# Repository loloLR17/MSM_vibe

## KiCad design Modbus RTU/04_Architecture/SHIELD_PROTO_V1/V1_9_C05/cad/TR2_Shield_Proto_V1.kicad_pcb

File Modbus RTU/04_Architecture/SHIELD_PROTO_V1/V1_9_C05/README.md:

# TR2 shield V1.9 — candidat corrigé sur CAO officielle C05

**NON LIBÉRÉ POUR FABRICATION.** Lire [la décision et les contrôles](DECISION_V19.md), [la provenance ST](PROVENANCE.md) et [le gabarit corrigé100%](exports/GABARITS_C05_V19_100POURCENT.pdf).

Ce dossier est le nouveau candidat éditable autonome. Les fichiers du dossierparent V1.4 et ses exports V1.8 sont historiques et préservés ; ne pas les prendre pour la correctionV1.9. Schéma/projet copiés sans changement électrique, PCB et routes localement corrigés. Le cartouche du schéma demeureV1.4 car le schéma est inchangé ; le PCB porteV1.9DRAFT.

Pour reproduire dans une copie isolée de ce dossier, **conserver le `design.json` V1.9 fourni**. Retirer le cuivre du **PCB candidat uniquement** avec `tools/strip_candidate_copper.py <candidatePCB>`, puis appliquer les positions absolues et trous avec `tools/patch_native.py <dossierV19>` (PythonKiCad10). Exécuter `tools/route_local.py` (Python+numpy+shapely ; lit les routes historiques du dossierparent), puis `tools/apply_routes.py <dossierV19>` avecPythonKiCad. Exécuter `tools/export_design.py`, `tools/read_board.py <dossierV19>` avecPythonKiCad, puis `tools/verify_exports.py`, `tools/verify_v19.py` et `tools/generate_templates.py` avecPyMuPDF. `patch_native` écrit `docs/pcb_geometry.json`, base de l’adaptation locale. L’application des routes suppose un candidat sans anciencuivre pour éviter un double routage. Le schéma et le projet fournis sont inchangés ; ne pas remplacer le designV1.9 par celuiV1.4. Ne jamais lancer ces scripts sur les originaux historiques.

Les originauxST restent en dehorsGit, sous `/home/lolo/dev/msm/reports/TR2-shield-v19-20261105`. Pour reproduire l’extraction CFB/ODB : `PYTHONPATH=/home/lolo/dev/msm/cache/shield-pylibs python3 tools/extract_st.py <ce-repertoire>` après avoir vérifié les deux SHA256 et extrait les archives conformément àPROVENANCE. Les preuves d’échecs et corrections de l’outillage sont conservées ; aucun test ou règle historique affaibli.

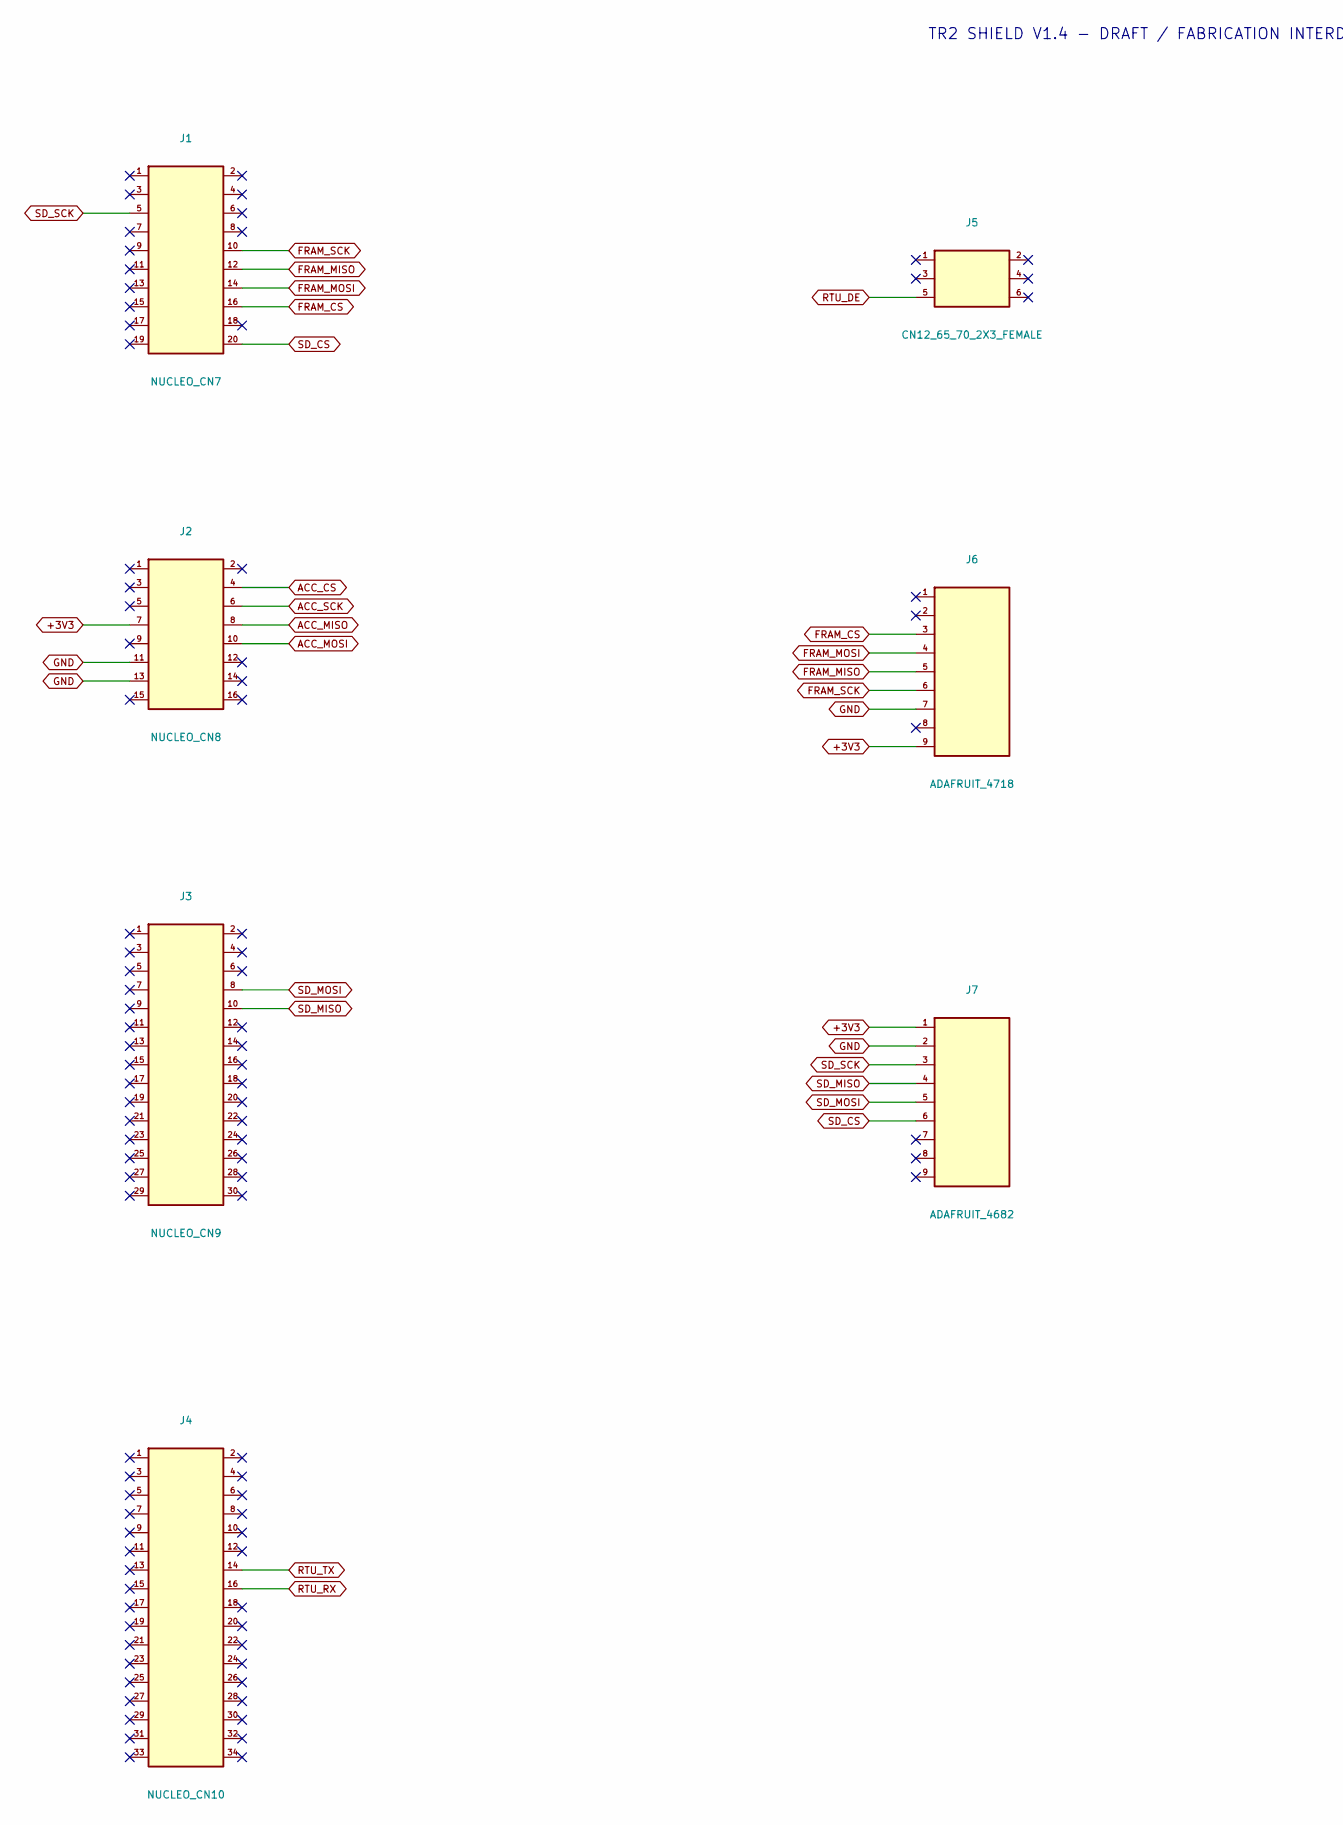
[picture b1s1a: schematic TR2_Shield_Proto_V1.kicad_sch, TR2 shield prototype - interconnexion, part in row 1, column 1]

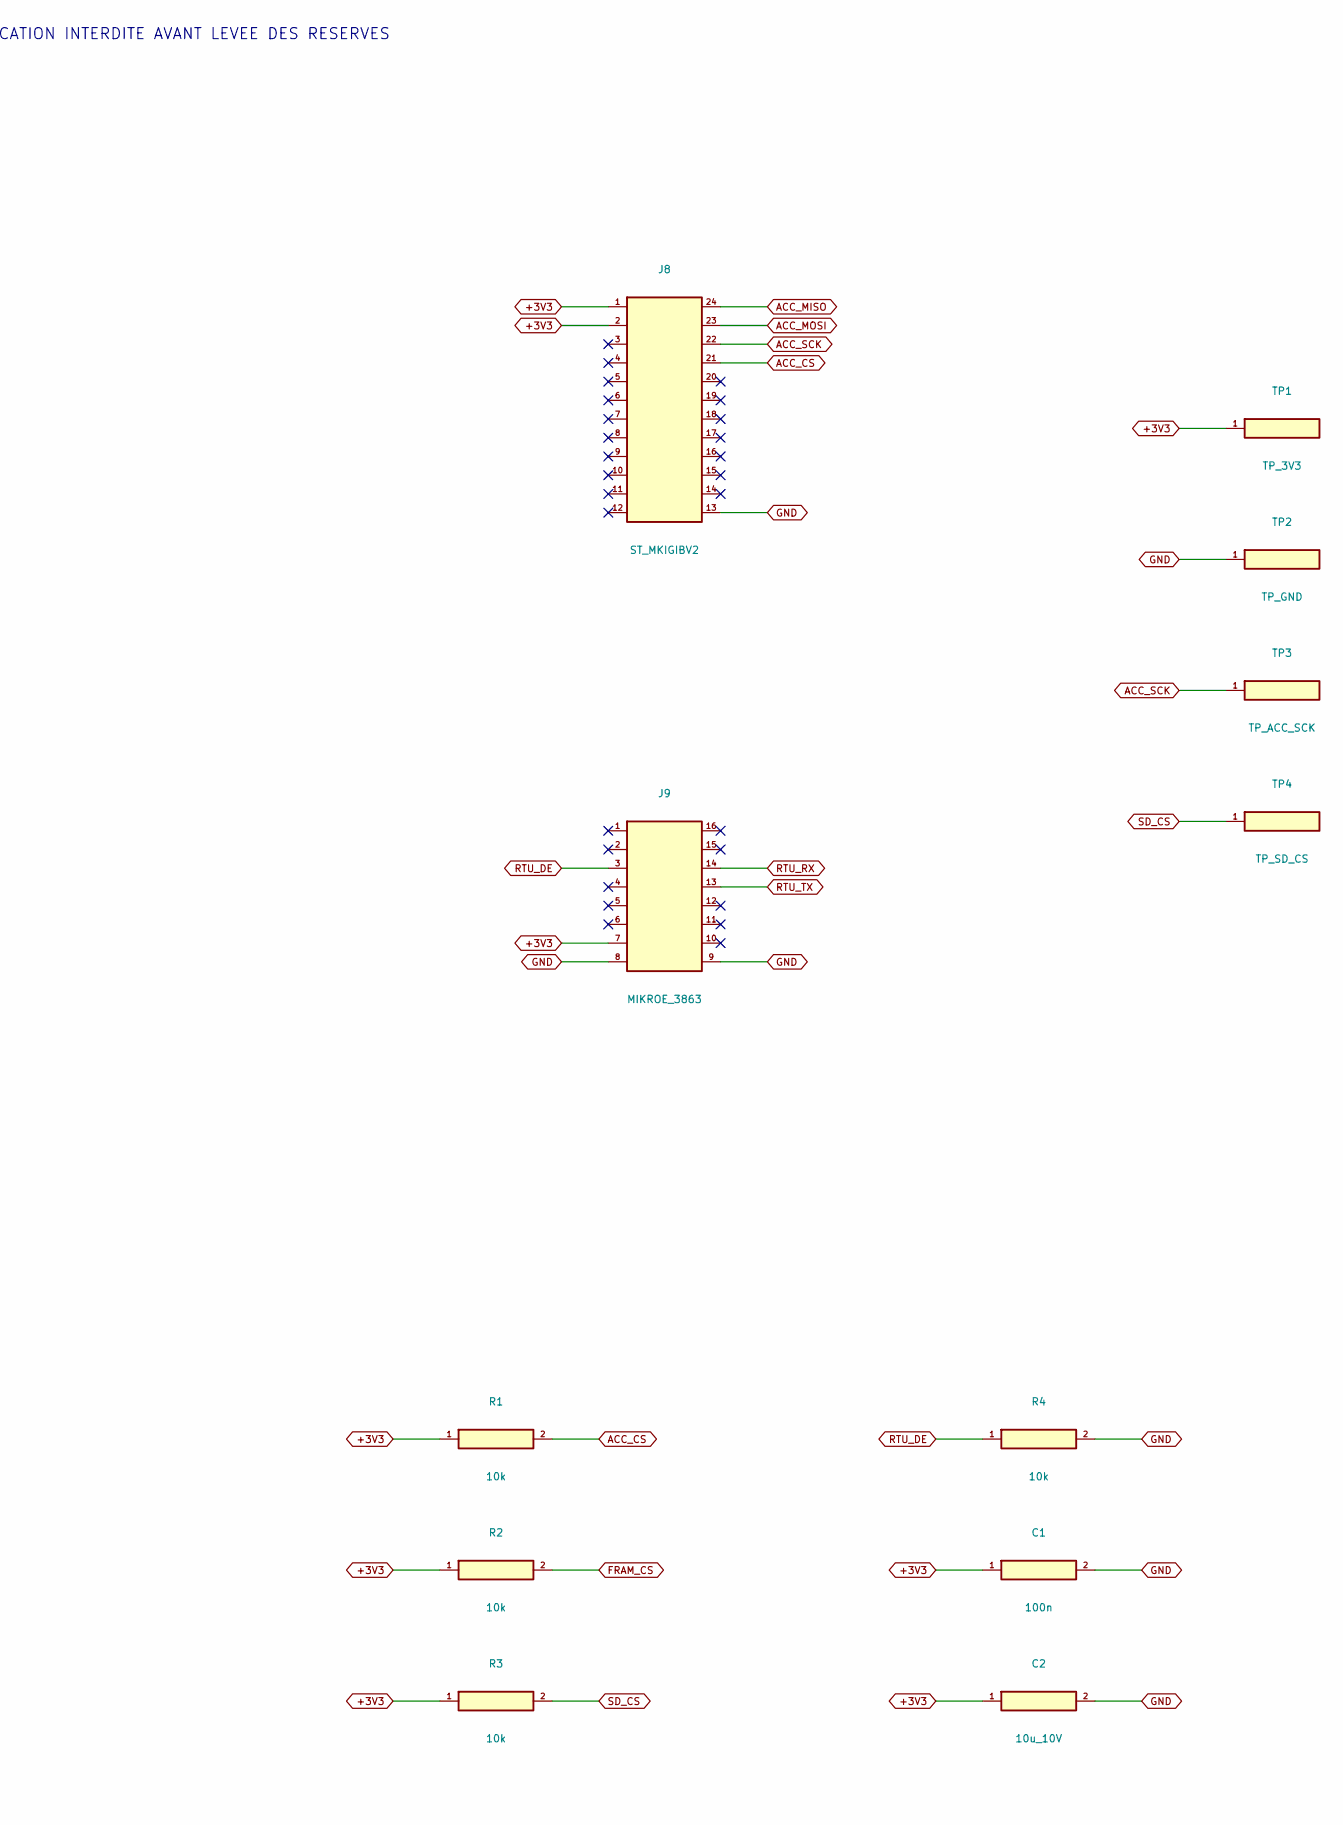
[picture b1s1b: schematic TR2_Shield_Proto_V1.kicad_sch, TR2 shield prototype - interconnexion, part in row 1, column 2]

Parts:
C1: 100n; C1_100n
C2: 10u_10V; C2_10u_10V
J1: NUCLEO_CN7; J1_NUCLEO_CN7
J2: NUCLEO_CN8; J2_NUCLEO_CN8
J3: NUCLEO_CN9; J3_NUCLEO_CN9
J4: NUCLEO_CN10; J4_NUCLEO_CN10
J5: CN12_65_70_2X3_FEMALE; J5_CN12_65_70_2X3_FEMALE
J6: ADAFRUIT_4718; J6_ADAFRUIT_4718
J7: ADAFRUIT_4682; J7_ADAFRUIT_4682
J8: ST_MKIGIBV2; J8_ST_MKIGIBV2
J9: MIKROE_3863; J9_MIKROE_3863
R1: 10k; R1_10k
R2: 10k; R2_10k
R3: 10k; R3_10k
R4: 10k; R4_10k
TP1: TP_3V3; TP1_TP_3V3
TP2: TP_GND; TP2_TP_GND
TP3: TP_ACC_SCK; TP3_TP_ACC_SCK
TP4: TP_SD_CS; TP4_TP_SD_CS

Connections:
+3V3: C1.1 (+3V3), C2.1 (+3V3), J2.7 (+3V3), J6.9 (+3V3), J7.1 (+3V3), J8.1 (+3V3), J8.2 (+3V3), J9.7 (+3V3), R1.1 (+3V3), R2.1 (+3V3), R3.1 (+3V3), TP1.1
ACC_CS: J2.4 (ACC_CS), J8.21 (ACC_CS), R1.2 (ACC_CS)
ACC_MISO: J2.8 (ACC_MISO), J8.24 (ACC_MISO)
ACC_MOSI: J2.10 (ACC_MOSI), J8.23 (ACC_MOSI)
ACC_SCK: J2.6 (ACC_SCK), J8.22 (ACC_SCK), TP3.1
FRAM_CS: J1.16 (FRAM_CS), J6.3 (FRAM_CS), R2.2 (FRAM_CS)
FRAM_MISO: J1.12 (FRAM_MISO), J6.5 (FRAM_MISO)
FRAM_MOSI: J1.14 (FRAM_MOSI), J6.4 (FRAM_MOSI)
FRAM_SCK: J1.10 (FRAM_SCK), J6.6 (FRAM_SCK)
GND: C1.2 (GND), C2.2 (GND), J2.11 (GND), J2.13 (GND), J6.7 (GND), J7.2 (GND), J8.13 (GND), J9.8 (GND), J9.9 (GND), R4.2 (GND), TP2.1
RTU_DE: J5.5 (RTU_DE), J9.3 (RTU_DE), R4.1 (RTU_DE)
RTU_RX: J4.16 (RTU_RX), J9.14 (RTU_RX)
RTU_TX: J4.14 (RTU_TX), J9.13 (RTU_TX)
SD_CS: J1.20 (SD_CS), J7.6 (SD_CS), R3.2 (SD_CS), TP4.1
SD_MISO: J3.10 (SD_MISO), J7.4 (SD_MISO)
SD_MOSI: J3.8 (SD_MOSI), J7.5 (SD_MOSI)
SD_SCK: J1.5 (SD_SCK), J7.3 (SD_SCK)

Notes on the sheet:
TR2 SHIELD V1.4 - DRAFT / FABRICATION INTERDITE AVANT LEVEE DES RESERVES

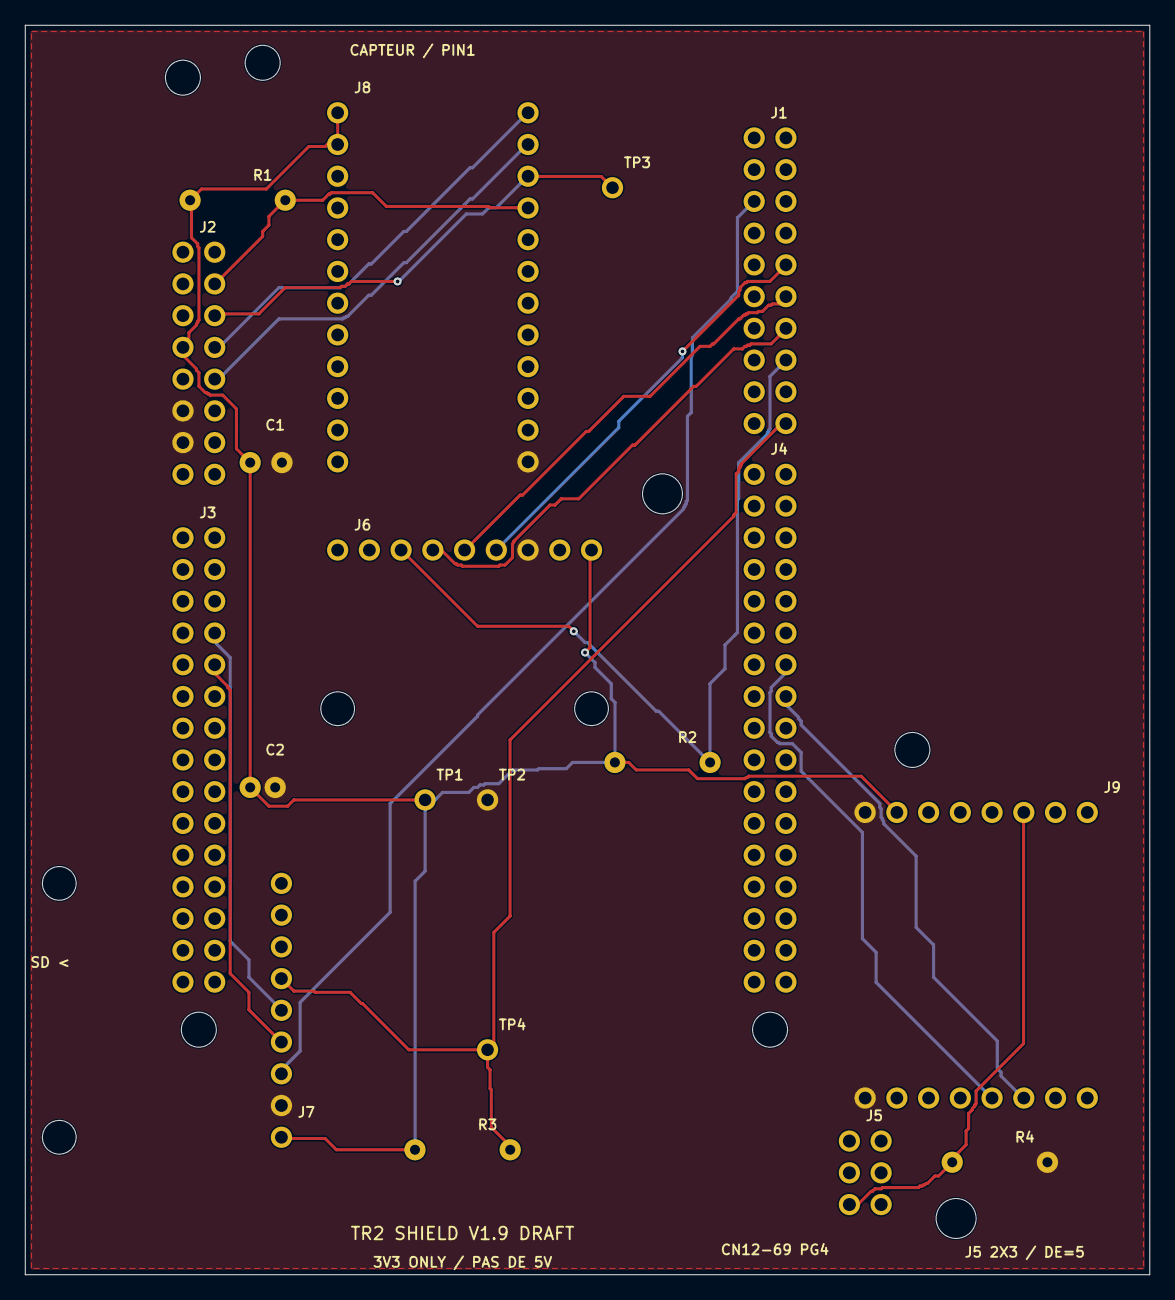
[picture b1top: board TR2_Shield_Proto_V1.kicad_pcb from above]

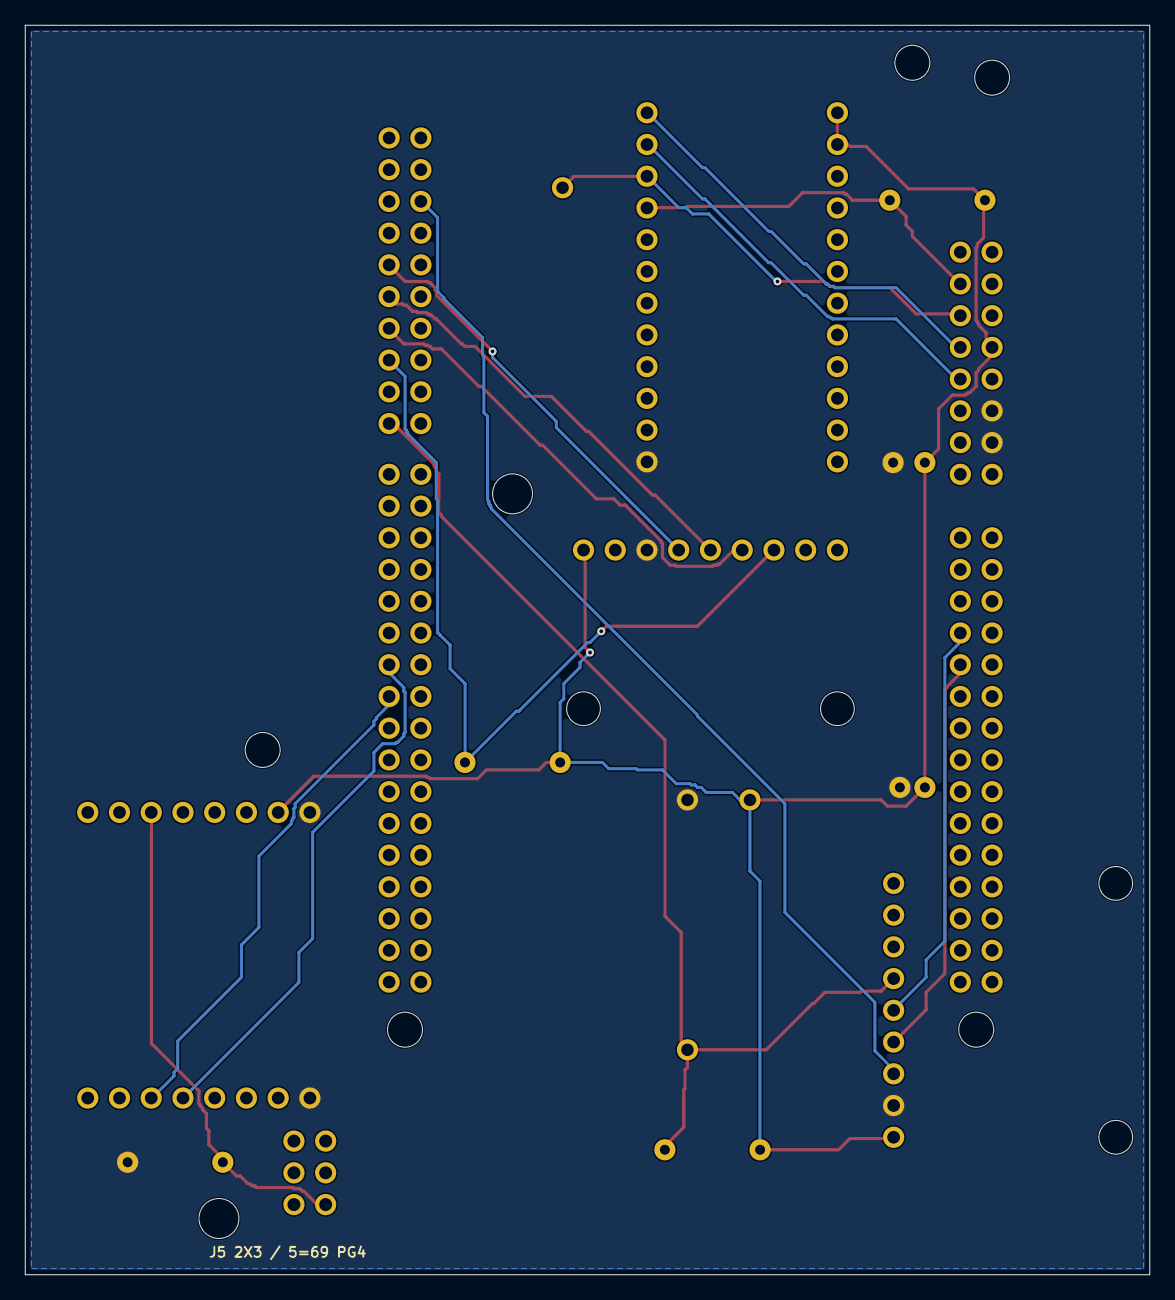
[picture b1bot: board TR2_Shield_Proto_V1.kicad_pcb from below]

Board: 2 copper layers, 90.0 x 100.0 mm, 19 parts (5 on the bottom side), 17 nets.
